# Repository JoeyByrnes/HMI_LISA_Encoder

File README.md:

# HMI_LISA_Encoder
Design Files for an AS5147U encoder for the RoboDesign Lab HMI Actuators.
<br>
- All outputs support 14 bits and can be used simultaneously. 
- All signals/power routed to conenctors are protected from ESD.

- Output Options:
    - Differential ABI
    - Single-Ended ABI
    - Absolute SPI
<br>

- Power Input Options:
    - 3.3v
    - 5v
<br>

<br>

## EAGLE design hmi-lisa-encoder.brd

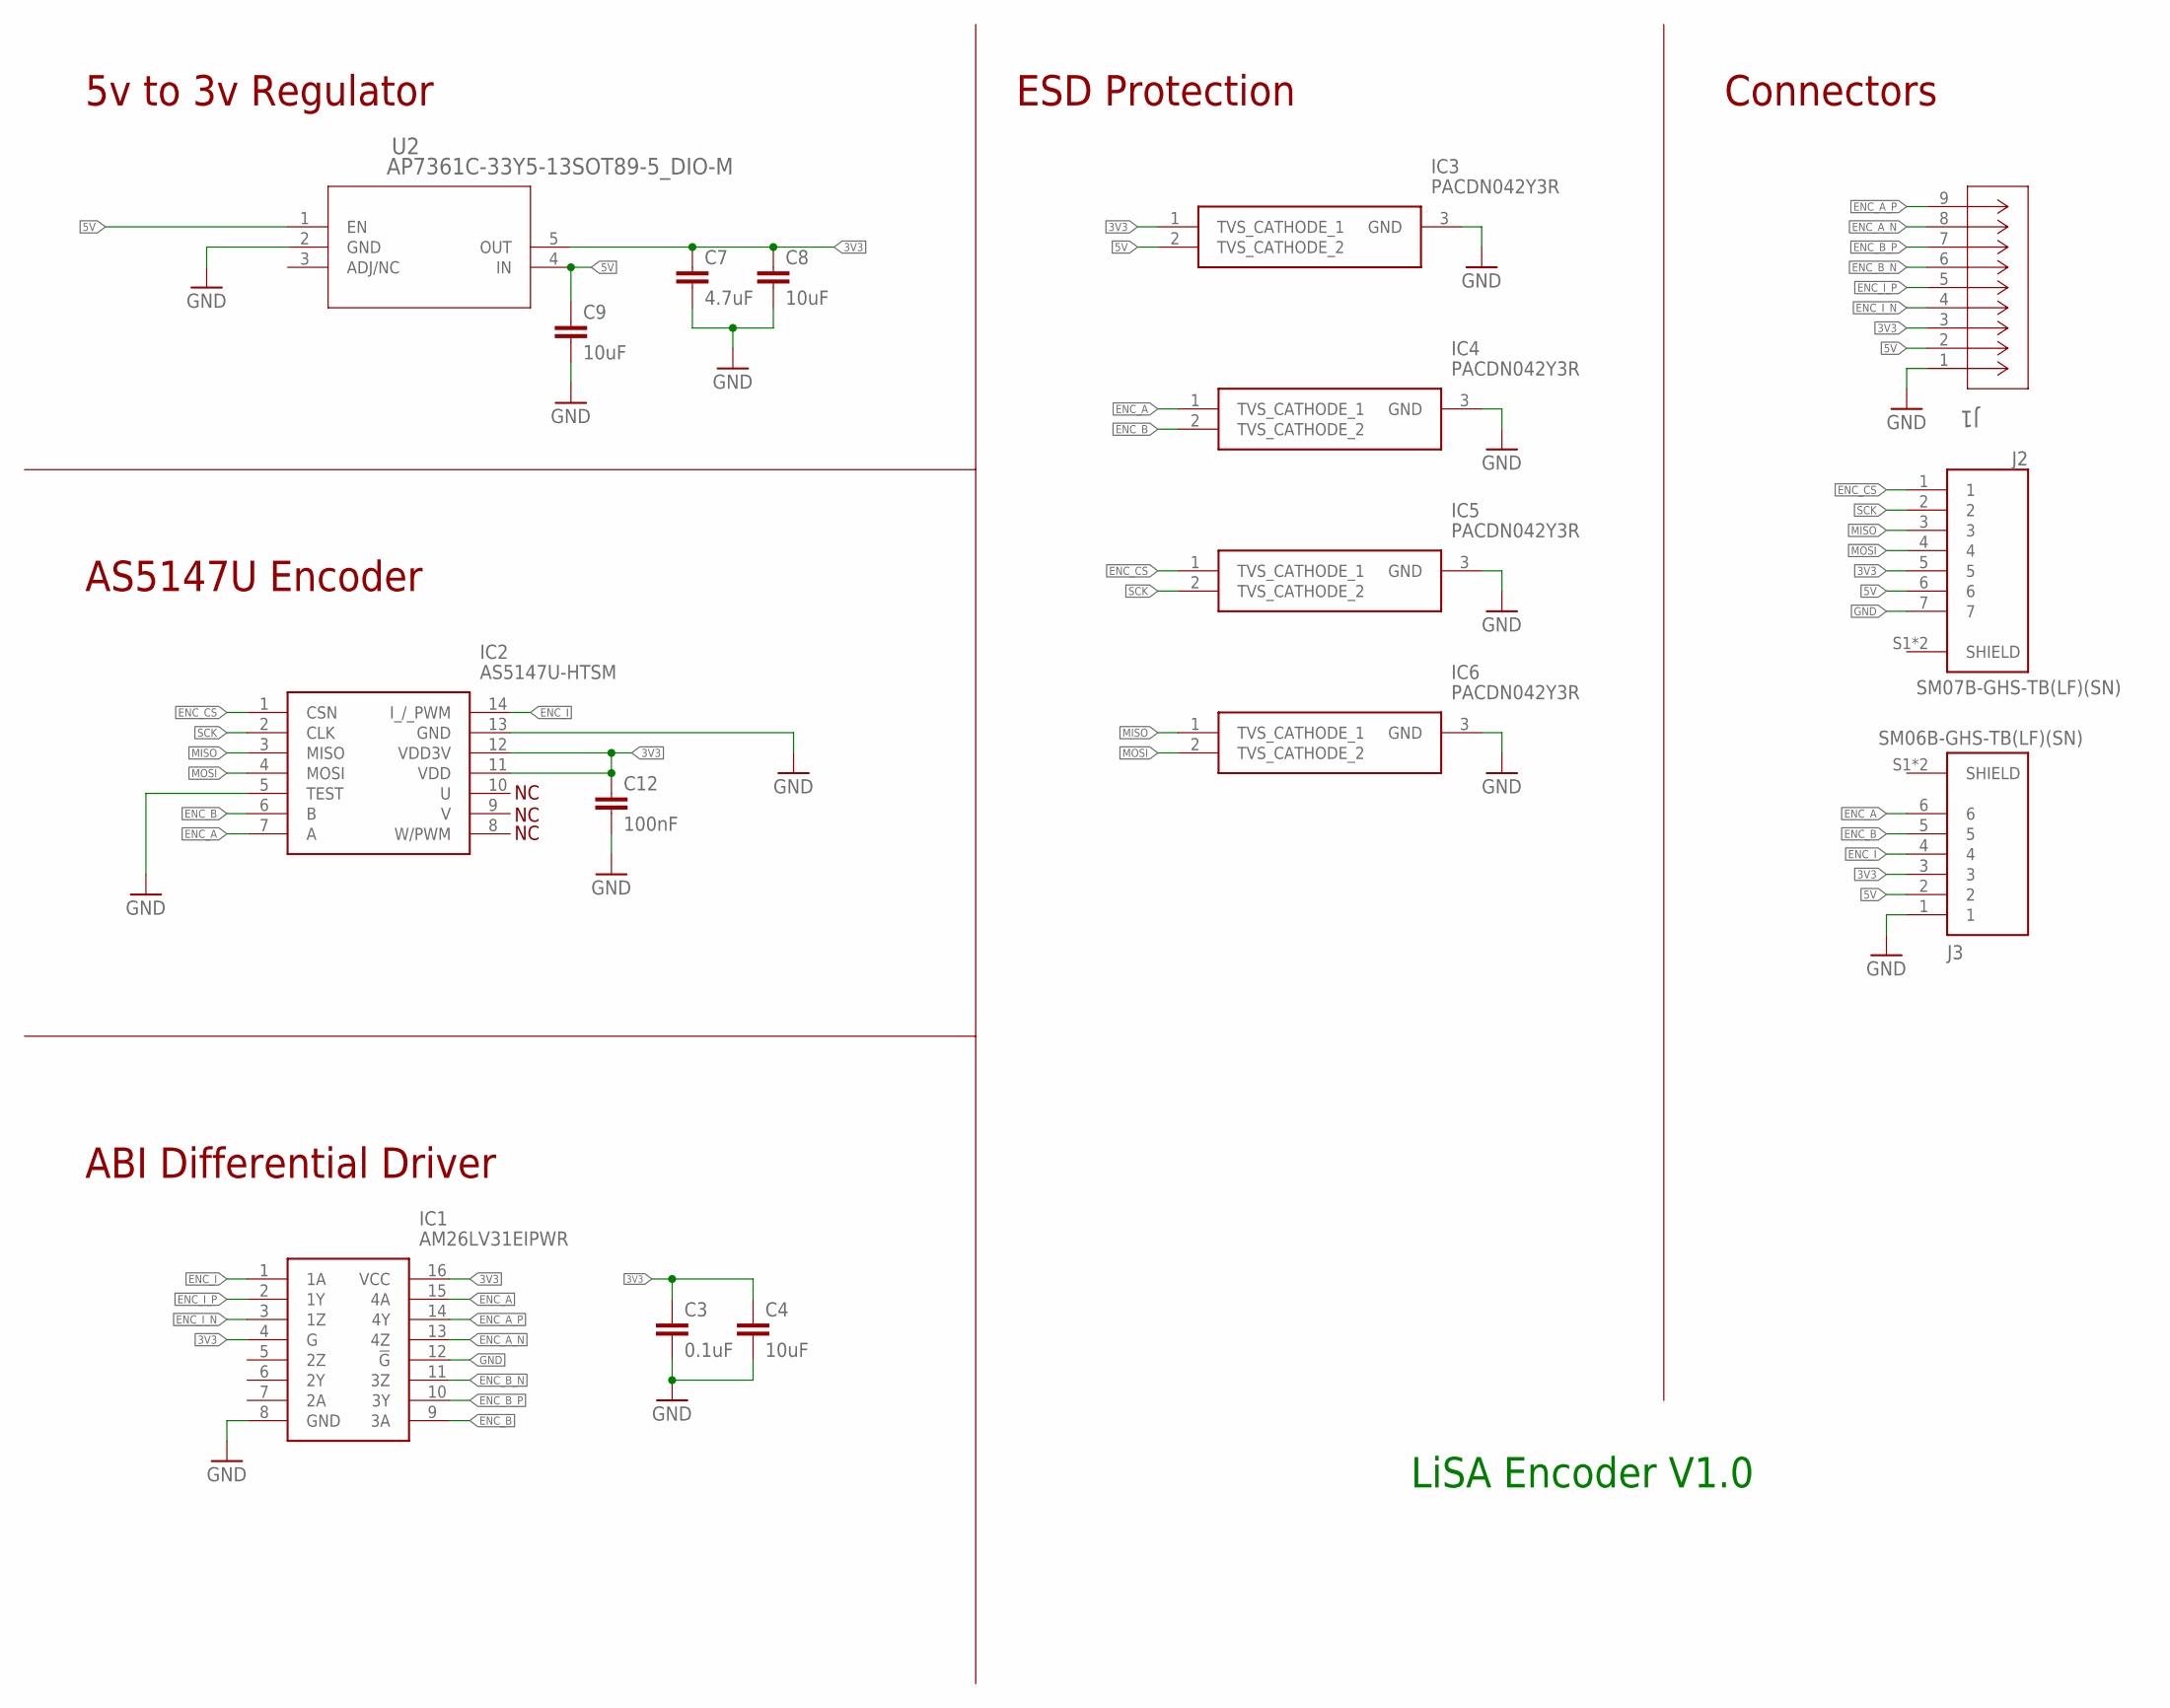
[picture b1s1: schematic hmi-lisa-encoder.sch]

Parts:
C3: 0.1uF; C0603
C4, C8, C9: 10uF; C0603
C7: 4.7uF; C0603
C12: 100nF; C0603
IC1: AM26LV31EIPWR; SOP65P640X120-16N
IC2: AS5147U-HTSM; SOP65P640X120-14N
IC3, IC4, IC5, IC6: PACDN042Y3R; SOT96P237X111-3N
J1: SM09B-GHS-TB(LF)(SN); CONN_SM09B-GHS-TB_JST
J2: SM07B-GHS-TB(LF)(SN); JST_SM07B-GHS-TB(LF)(SN)
J3: SM06B-GHS-TB(LF)(SN); JST_SM06B-GHS-TB(LF)(SN)
U2: AP7361C-33Y5-13SOT89-5_DIO-M; SOT89-5_DIO-M

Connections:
3V3: C3.1, C4.1, C7.1, C8.1, C12.1, IC1.4 (G), IC1.16 (VCC), IC2.11 (VDD), IC2.12 (VDD3V), IC3.1 (TVS_CATHODE_1), J1.3, J2.5, J3.3, U2.5 (OUT)
5V: C9.1, IC3.2 (TVS_CATHODE_2), J1.2, J2.6, J3.2, U2.1 (EN), U2.4 (IN)
ENC_A: IC1.15 (4A), IC2.7 (A), IC4.1 (TVS_CATHODE_1), J3.6
ENC_A_N: IC1.13 (4Z), J1.8
ENC_A_P: IC1.14 (4Y), J1.9
ENC_B: IC1.9 (3A), IC2.6 (B), IC4.2 (TVS_CATHODE_2), J3.5
ENC_B_N: IC1.11 (3Z), J1.6
ENC_B_P: IC1.10 (3Y), J1.7
ENC_CS: IC2.1 (CSN), IC5.1 (TVS_CATHODE_1), J2.1
ENC_I: IC1.1 (1A), IC2.14 (I_/_PWM), J3.4
ENC_I_N: IC1.3 (1Z), J1.4
ENC_I_P: IC1.2 (1Y), J1.5
GND: C3.2, C4.2, C7.2, C8.2, C9.2, C12.2, IC1.8 (GND), IC1.12 (!G), IC2.5 (TEST), IC2.13 (GND), IC3.3 (GND), IC4.3 (GND), IC5.3 (GND), IC6.3 (GND), J1.1, J2.7, J3.1, U2.2 (GND)
MISO: IC2.3 (MISO), IC6.1 (TVS_CATHODE_1), J2.3
MOSI: IC2.4 (MOSI), IC6.2 (TVS_CATHODE_2), J2.4
SCK: IC2.2 (CLK), IC5.2 (TVS_CATHODE_2), J2.2
SHIELD: J2.S1 (SHIELD), J2.S2 (SHIELD)

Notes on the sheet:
5v to 3v Regulator
LiSA Encoder V1.0
ESD Protection
AS5147U Encoder
Connectors
ABI Differential Driver

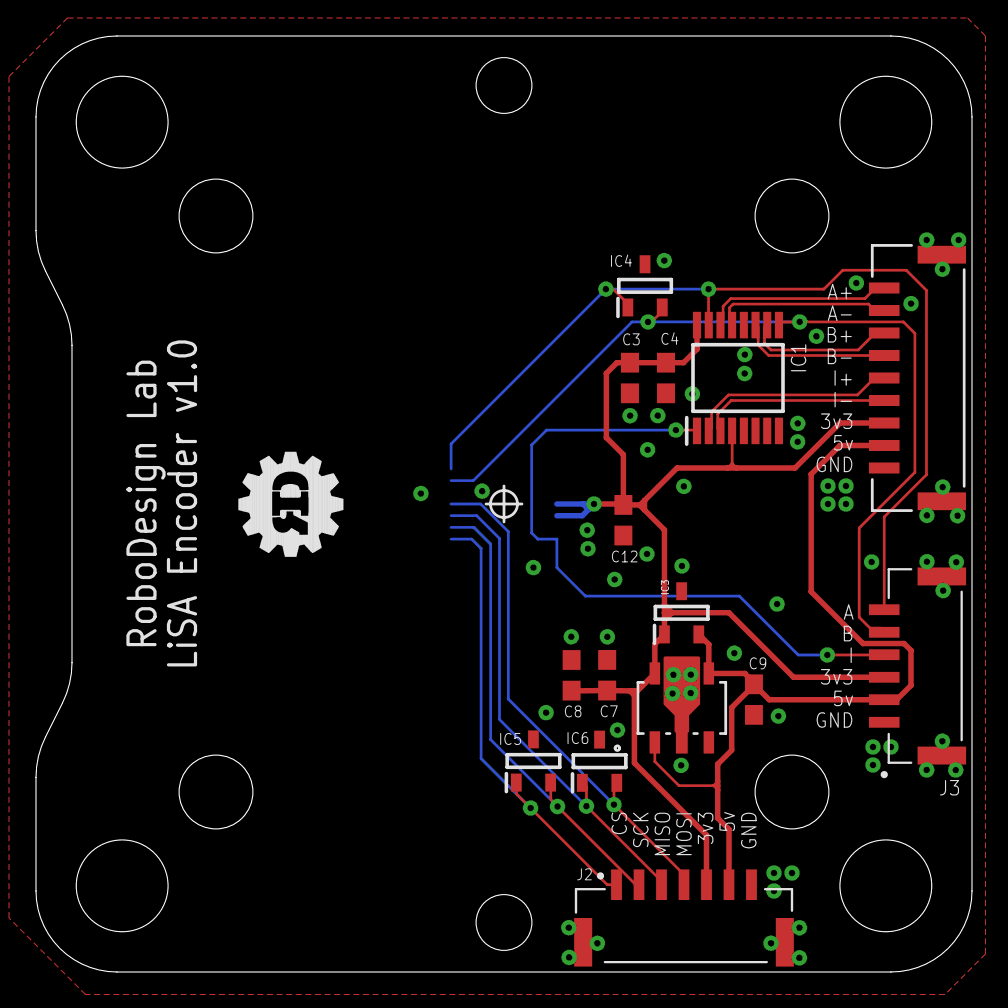
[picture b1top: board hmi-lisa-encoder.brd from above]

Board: 2 copper layers, 52.0 x 52.0 mm, 16 parts (1 on the bottom side), 17 nets.

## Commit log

2023-10-11 Added routed source files, needs design review

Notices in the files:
parts and their libraries:
COPYRIGHT: Copyright (C) 2023 Ultra Librarian. All rights reserved.
